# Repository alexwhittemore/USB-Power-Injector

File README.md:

USB-Power-Injector
==================

USB 2.0 Power Injector

This board constitutes a very simple design to inject power (from a mini-B cable) into any A connection.

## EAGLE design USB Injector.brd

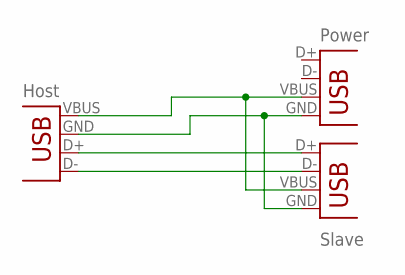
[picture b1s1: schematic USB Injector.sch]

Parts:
X1: USB-A-SMD; USB-A-S-NOSILK-FEMALE
X2: USB-A-H
X3: USBSMD; USB-MINIB

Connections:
GND: X1.GND, X2.GND (VBUS), X3.GND
unnamed: X1.D-, X2.D- (D+)
unnamed: X1.D+, X2.D+ (D-)
VDD: X1.VBUS, X2.VBUS (GND), X3.VBUS

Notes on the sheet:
Host
Slave
Power

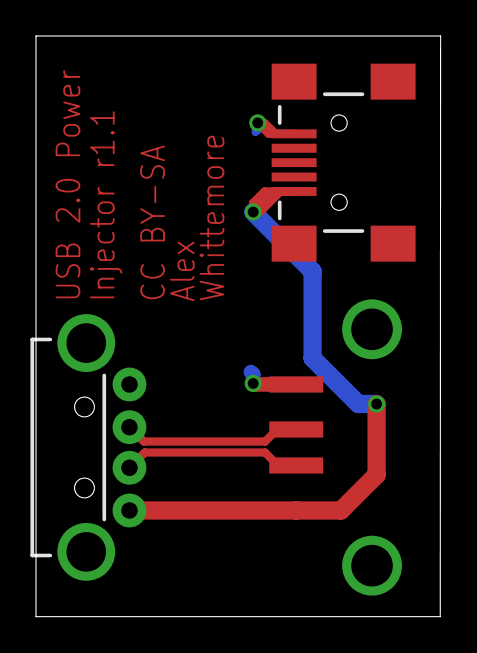
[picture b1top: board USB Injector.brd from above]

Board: 2 copper layers, 22.5 x 32.3 mm, 3 parts (0 on the bottom side), 4 nets.

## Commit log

2013-06-18 Initial commit (r1.1). Should be USB 2.0 ready.
2013-06-20 Ignore eagle.epf

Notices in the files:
USB Injector.brd:
CC BY-SA
parts and their libraries:
SparkFun-Connectors: Licensing: CC v3.0 Share-Alike You are welcome to use this library for commercial purposes.
AlexW-Eagle-Libraries: Released under the Creative Commons
AlexW-Eagle-Libraries: http://creativecommons.org/licenses/by-sa/3.0
